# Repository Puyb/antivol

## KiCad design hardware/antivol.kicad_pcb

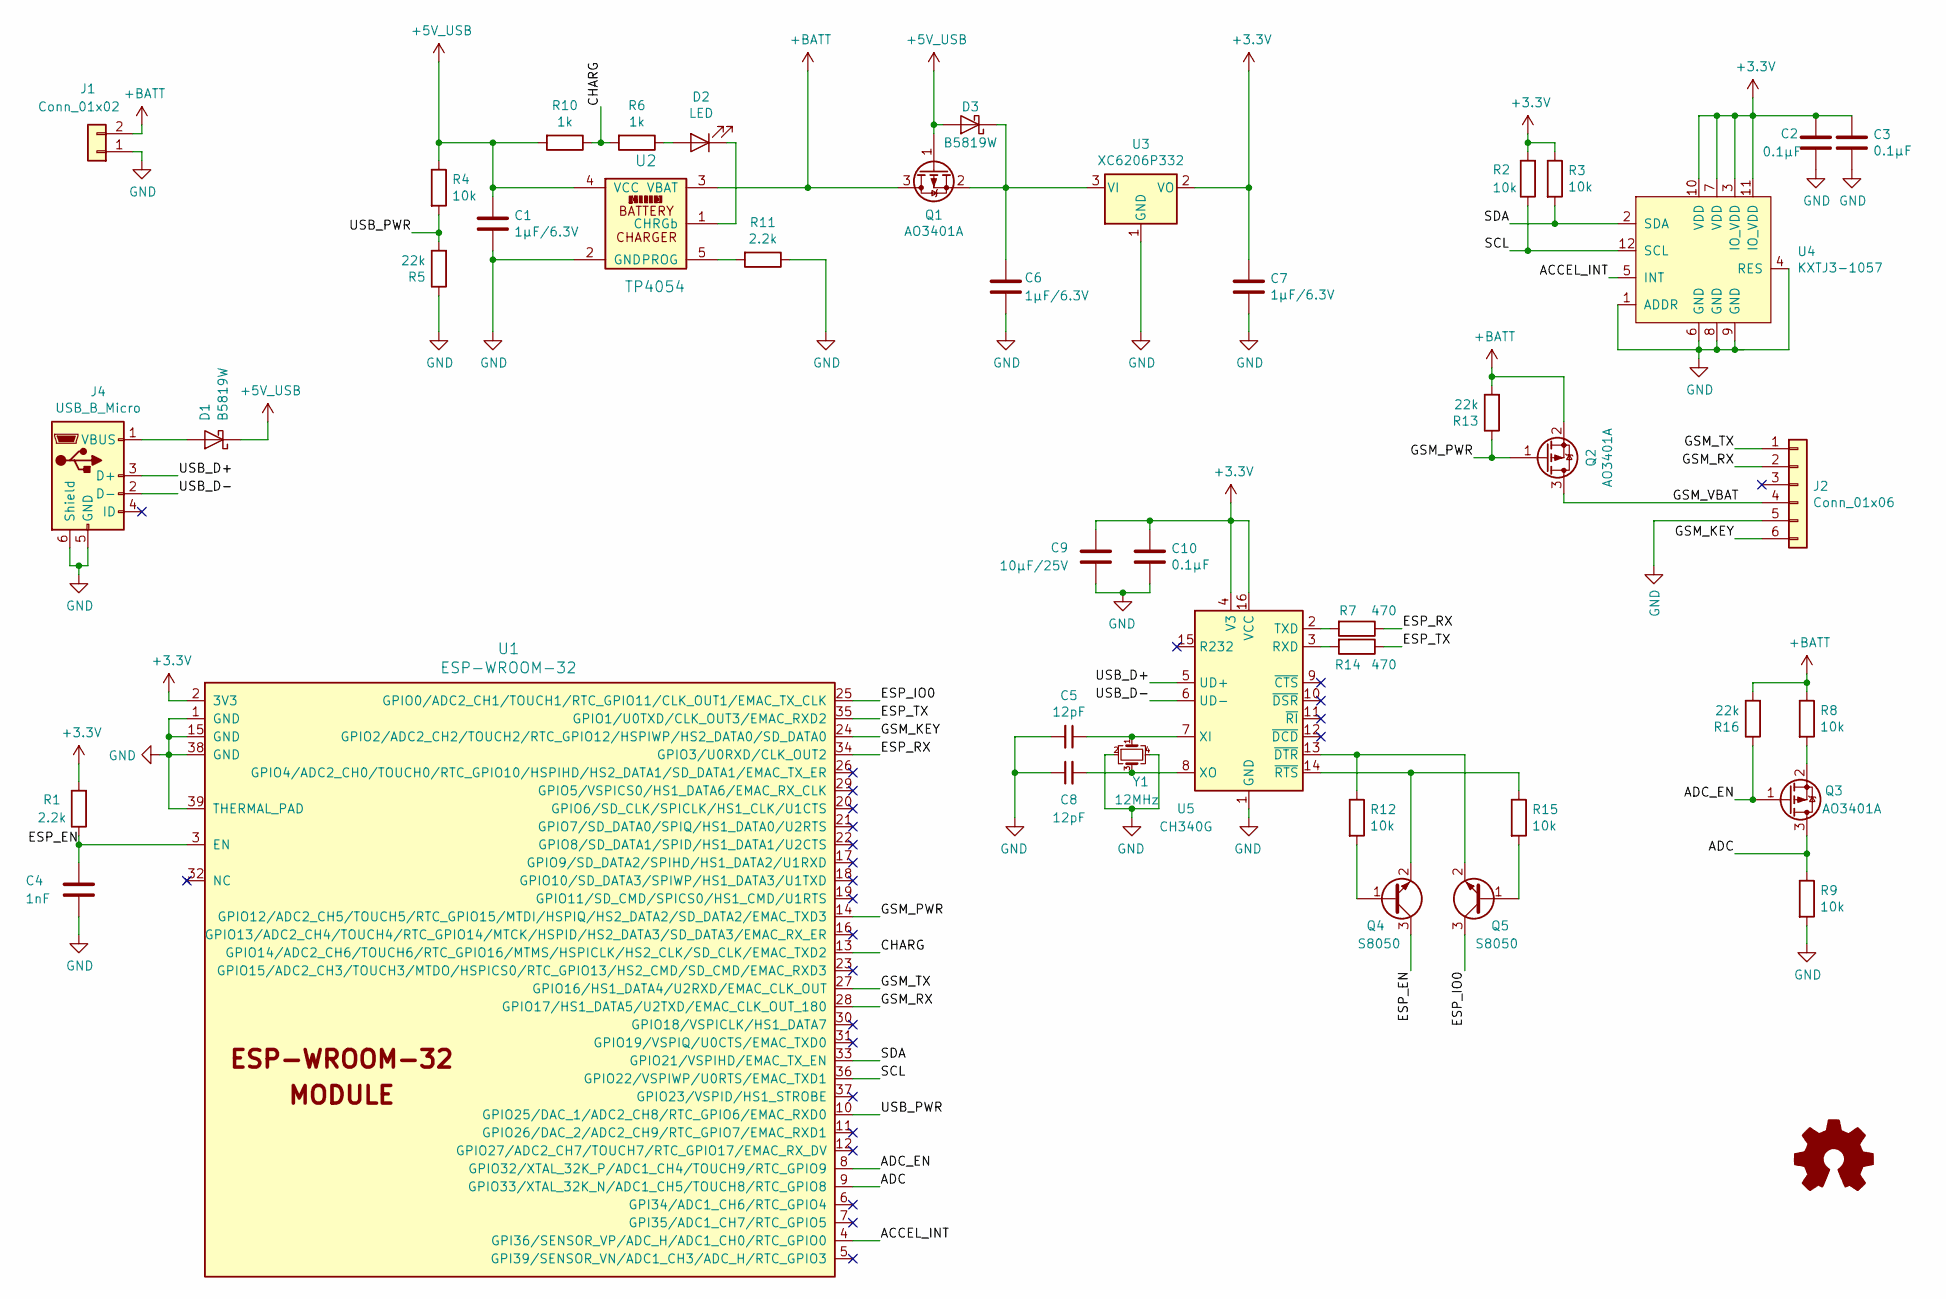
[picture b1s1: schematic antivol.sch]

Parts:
C1, C6, C7: 1µF/6.3V; C_0603_1608Metric; LCSC C15849
C2, C3, C10: 0.1µF; C_0603_1608Metric; LCSC C14663
C4: 1nF; C_0603_1608Metric; LCSC C1588
C5, C8: 12pF; C_0603_1608Metric; LCSC C38523
C9: 10µF/25V; C_0805_2012Metric; LCSC C15850
D1, D3: B5819W; D_SOD-123; LCSC C8598
D2: LED; D_0603_1608Metric; LCSC C72038
J1: Conn_01x02; PinHeader_1x02_P2.54mm_Vertical
J2: Conn_01x06; PinHeader_1x06_P2.54mm_Vertical
J4: USB_B_Micro; USB_Micro-B_Molex-105017-0001
Q1, Q2, Q3: AO3401A; SOT-23; LCSC C15127
Q4, Q5: S8050; SOT-23; LCSC C2146
R1, R11: 2.2k; R_0603_1608Metric; LCSC C4190
R2, R3, R4, R8, R9, R12, R15: 10k; R_0603_1608Metric; LCSC C25804
R5, R13, R16: 22k; R_0603_1608Metric; LCSC C31850
R6, R10: 1k; R_0603_1608Metric; LCSC C21190
R7, R14: 470; R_0603_1608Metric; LCSC C23179
U1: ESP-WROOM-32; ESP-WROOM-32_MODULE
U2: TP4054; SOT-23-5; LCSC C32574
U3: XC6206P332; SOT-23; LCSC C5446
U4: KXTJ3-1057; LGA-12_2x2mm_P0.5mm; LCSC C442603
U5: CH340G; SOIC-16_3.9x9.9mm_P1.27mm; LCSC C14267
Y1: 12MHz; Crystal_SMD_3225-4Pin_3.2x2.5mm; LCSC C9002

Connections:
+3V3: C2.2, C3.2, C7.1, C9.2, C10.1, R1.2, R2.2, R3.1, U1.2 (3V3), U3.2 (VO), U4.3 (IO_VDD), U4.7 (VDD), U4.10 (VDD), U4.11 (IO_VDD), U5.4 (V3), U5.16 (VCC)
+5V_USB: C1.1, D1.1 (K), D3.2 (A), Q1.1 (G), R4.1, R10.2, U2.4 (VCC)
+BATT: J1.2, Q1.3 (D), Q2.2 (S), R8.1, R13.2, R16.2, U2.3 (VBAT)
/ACCEL_INT: U1.4 (GPI36/SENSOR_VP/ADC_H/ADC1_CH0/RTC_GPIO0), U4.5 (INT)
/ADC: Q3.3 (D), R9.1, U1.9 (GPIO33/XTAL_32K_N/ADC1_CH5/TOUCH8/RTC_G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)
/ADC_EN: Q3.1 (G), R16.1, U1.8 (GPIO32/XTAL_32K_P/ADC1_CH4/TOUCH9/RTC_G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)
/CHARG: R6.2, R10.1, U1.13 (GPIO14/ADC2_CH6/TOUCH6/RTC_GPIO16/MTMS/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)
/ESP_EN: C4.2, Q4.3 (C), R1.1, U1.3 (EN)
/ESP_IO0: Q5.3 (C), U1.25 (GPIO0/ADC2_CH1/TOUCH1/RTC_GPIO11/CLK_OU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)
/ESP_RX: R7.1, U1.34 (GPIO3/U0RXD/CLK_OUT2)
/ESP_TX: R14.1, U1.35 (GPIO1/U0TXD/CLK_OUT3/EMAC_RXD2)
/GSM_KEY: J2.6, U1.24 (GPIO2/ADC2_CH2/TOUCH2/RTC_GPIO12/HSPIWP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)
/GSM_PWR: Q2.1 (G), R13.1, U1.14 (GPIO12/ADC2_CH5/TOUCH5/RTC_GPIO15/MTDI/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)
/GSM_RX: J2.2, U1.28 (GPIO17/HS1_DATA5/U2TXD/EMAC_CLK_OUT_180)
/GSM_TX: J2.1, U1.27 (GPIO16/HS1_DATA4/U2RXD/EMAC_CLK_OUT)
/GSM_VBAT: J2.4, Q2.3 (D)
/SCL: R2.1, U1.36 (GPIO22/VSPIWP/U0RTS/EMAC_TXD1), U4.12 (SCL)
/SDA: R3.2, U1.33 (GPIO21/VSPIHD/EMAC_TX_EN), U4.2 (SDA)
/USB_D+: J4.3 (D+), U5.5 (UD+)
/USB_D-: J4.2 (D-), U5.6 (UD-)
/USB_PWR: R4.2, R5.2, U1.10 (GPIO25/DAC_1/ADC2_CH8/RTC_GPIO6/EMAC_RX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)
GND: C1.2, C2.1, C3.1, C4.1, C5.2, C6.2, C7.2, C8.1, C9.1, C10.2, J1.1, J2.5, J4.5 (GND), J4.6 (Shield), R5.1, R9.2, R11.1, U1.1 (GND), U1.15 (GND), U1.38 (GND), U1.39 (THERMAL_PAD), U2.2 (GND), U3.1 (GND), U4.1 (ADDR), U4.4 (RES), U4.6 (GND), U4.8 (GND), U4.9 (GND), U5.1 (GND), Y1.2, Y1.4
unnamed: C5.1, U5.7 (XI), Y1.1
unnamed: C6.1, D3.1 (K), Q1.2 (S), U3.3 (VI)
unnamed: C8.2, U5.8 (XO), Y1.3
unnamed: D1.2 (A), J4.1 (VBUS)
unnamed: D2.1 (K), U2.1 (CHRGb)
unnamed: D2.2 (A), R6.1
unnamed: Q3.2 (S), R8.2
unnamed: Q4.1 (B), R12.2
unnamed: Q4.2 (E), R15.1, U5.14 (~RTS)
unnamed: Q5.1 (B), R15.2
unnamed: Q5.2 (E), R12.1, U5.13 (~DTR)
unnamed: R7.2, U5.2 (TXD)
unnamed: R11.2, U2.5 (PROG)
unnamed: R14.2, U5.3 (RXD)

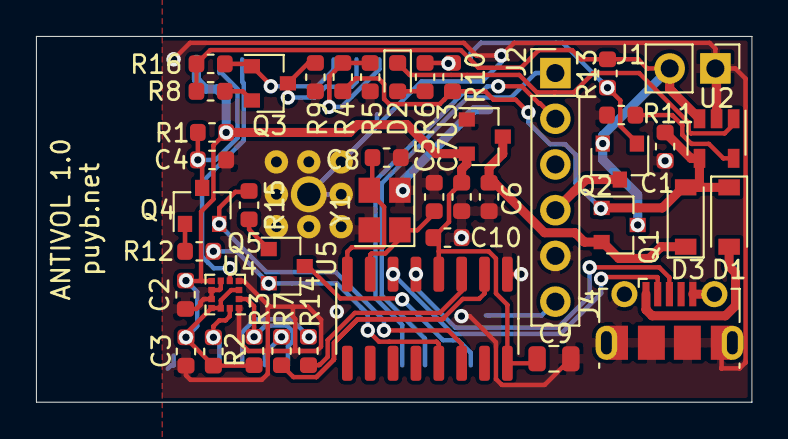
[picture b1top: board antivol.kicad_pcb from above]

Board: 2 copper layers, 39.8 x 20.3 mm, 43 parts (1 on the bottom side), 36 nets.

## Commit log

2019-11-23 Add charger
2019-12-07 final without usb
2019-12-08 cp2102
